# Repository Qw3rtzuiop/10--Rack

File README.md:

# 10--Rack
Various 10"-Rack stuff

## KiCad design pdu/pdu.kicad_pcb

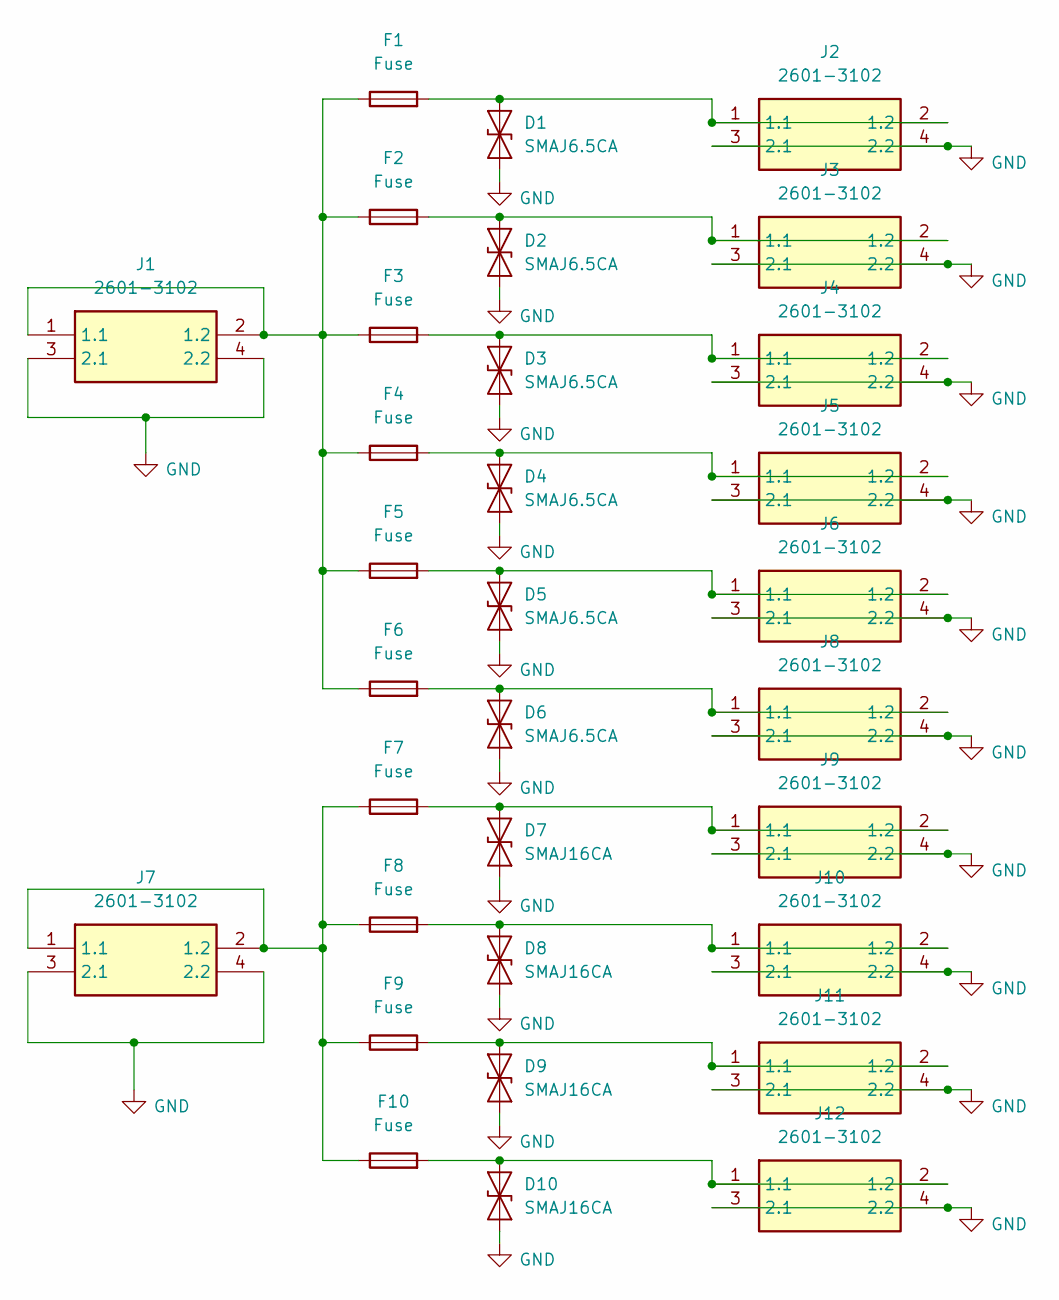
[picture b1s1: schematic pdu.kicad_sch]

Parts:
D1, D2, D3, D4, D5, D6: SMAJ6.5CA; D_SMA
D7, D8, D9, D10: SMAJ16CA; D_SMA
F1, F2, F3, F4, F5, F6, F7, F8, F9, F10: Fuse; Fuseholder_Littelfuse_100_series_5x20mm
J1, J2, J3, J4, J5, J6, J7, J8, J9, J10, J11, J12: 2601-3102; 26013102; Manufacturer_Part_Number 2601-3102

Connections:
GND: D1.1 (A1), D2.1 (A1), D3.1 (A1), D4.1 (A1), D5.1 (A1), D6.1 (A1), D7.1 (A1), D8.1 (A1), D9.1 (A1), D10.1 (A1), J1.3 (2.1), J1.4 (2.2), J2.3 (2.1), J2.4 (2.2), J3.3 (2.1), J3.4 (2.2), J4.3 (2.1), J4.4 (2.2), J5.3 (2.1), J5.4 (2.2), J6.3 (2.1), J6.4 (2.2), J7.3 (2.1), J7.4 (2.2), J8.3 (2.1), J8.4 (2.2), J9.3 (2.1), J9.4 (2.2), J10.3 (2.1), J10.4 (2.2), J11.3 (2.1), J11.4 (2.2), J12.3 (2.1), J12.4 (2.2)
unnamed: D1.2 (A2), F1.2, J2.1 (1.1), J2.2 (1.2)
unnamed: D2.2 (A2), F2.2, J3.1 (1.1), J3.2 (1.2)
unnamed: D3.2 (A2), F3.2, J4.1 (1.1), J4.2 (1.2)
unnamed: D4.2 (A2), F4.2, J5.1 (1.1), J5.2 (1.2)
unnamed: D5.2 (A2), F5.2, J6.1 (1.1), J6.2 (1.2)
unnamed: D6.2 (A2), F6.2, J8.1 (1.1), J8.2 (1.2)
unnamed: D7.2 (A2), F7.2, J9.1 (1.1), J9.2 (1.2)
unnamed: D8.2 (A2), F8.2, J10.1 (1.1), J10.2 (1.2)
unnamed: D9.2 (A2), F9.2, J11.1 (1.1), J11.2 (1.2)
unnamed: D10.2 (A2), F10.2, J12.1 (1.1), J12.2 (1.2)
unnamed: F1.1, F2.1, F3.1, F4.1, F5.1, F6.1, J1.1 (1.1), J1.2 (1.2)
unnamed: F7.1, F8.1, F9.1, F10.1, J7.1 (1.1), J7.2 (1.2)

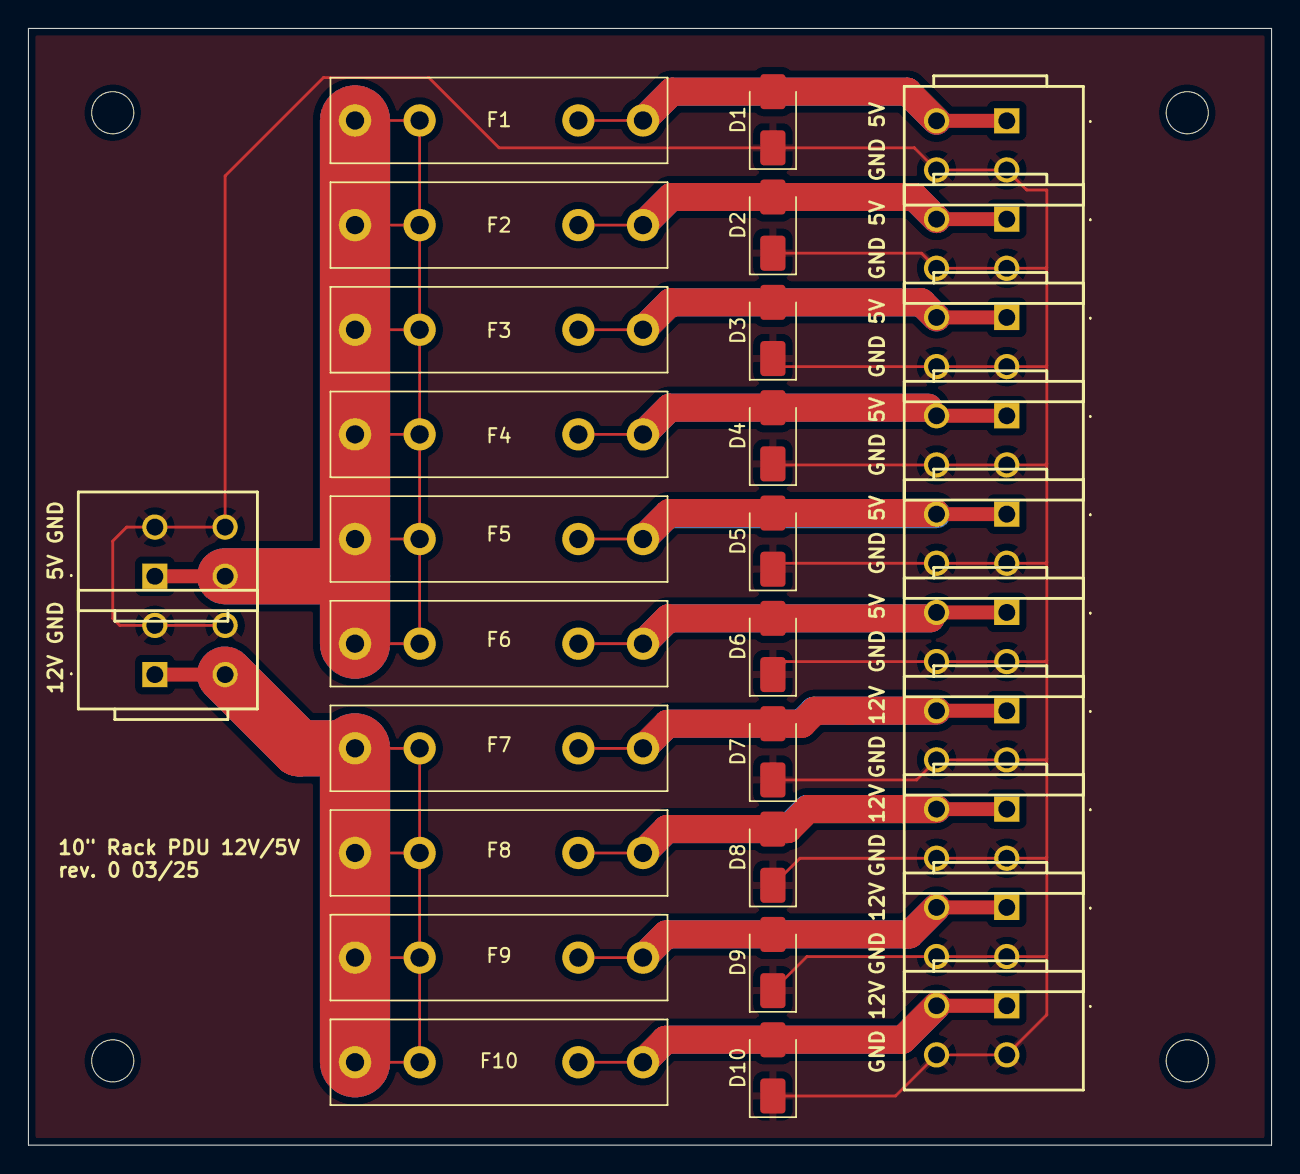
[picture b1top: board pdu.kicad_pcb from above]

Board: 2 copper layers, 88.5 x 79.5 mm, 32 parts (0 on the bottom side), 13 nets.

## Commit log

2025-02-09 fb7590 rev.0
2025-03-02 display.kicad_pcb, display.kicad_pro und 8 weitere dateien aktualisiert...
2025-03-02 display.kicad_pcb, display.zip und 2 weitere dateien aktualisiert...
2025-03-16 pdu.kicad_pcb, pdu.kicad_pro und 3 weitere dateien aktualisiert...
